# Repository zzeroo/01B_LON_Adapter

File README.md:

## Dateien
- 164.001.01B_ADP_LON_20100224.zip -> Original Dateien "Mack Ware GmbH"

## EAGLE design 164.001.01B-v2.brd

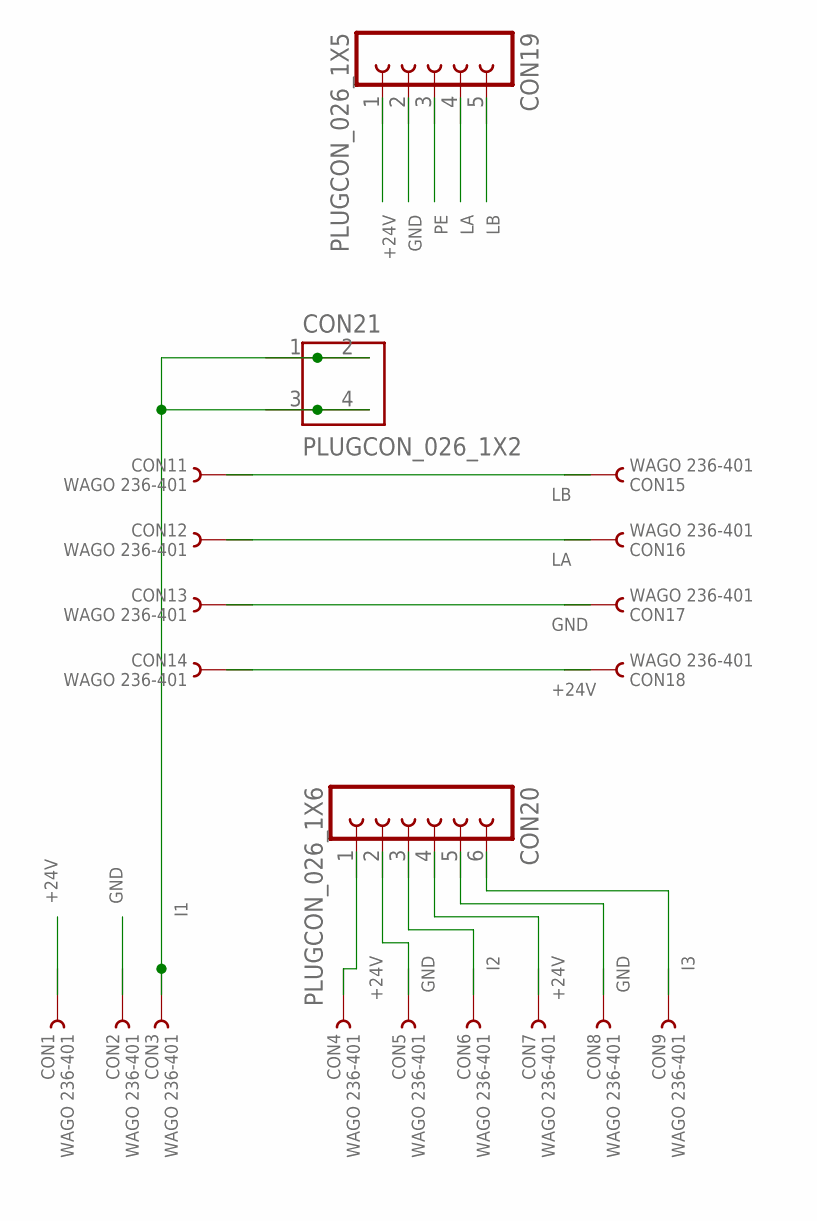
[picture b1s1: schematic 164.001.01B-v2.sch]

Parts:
CON1, CON2, CON3, CON4, CON5, CON6, CON7, CON8, CON9, CON11, CON12, CON13, CON14, CON15, CON16, CON17, CON18: WAGO 236-401; WAGO236
CON19: PLUGCON_026_1X5; PLUGCON1X5
CON20: PLUGCON_026_1X6; PLUGCON1X6
CON21: PLUGCON_026_1X2; PLUGCON1X2

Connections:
+24V: CON1.1, CON1.2, CON4.1, CON4.2, CON7.1, CON7.2, CON14.1, CON14.2, CON18.1, CON18.2, CON19.1, CON19.6, CON20.1, CON20.4, CON20.7, CON20.10
GND: CON2.1, CON2.2, CON5.1, CON5.2, CON8.1, CON8.2, CON13.1, CON13.2, CON17.1, CON17.2, CON19.2, CON19.7, CON20.2, CON20.5, CON20.8, CON20.11
I1: CON3.1, CON3.2, CON21.1, CON21.2 (1), CON21.3 (2), CON21.4 (2)
I2: CON6.1, CON6.2, CON20.3, CON20.9
I3: CON9.1, CON9.2, CON20.6, CON20.12
LA: CON12.1, CON12.2, CON16.1, CON16.2, CON19.4, CON19.9
LB: CON11.1, CON11.2, CON15.1, CON15.2, CON19.5, CON19.10
PE: CON19.3, CON19.8

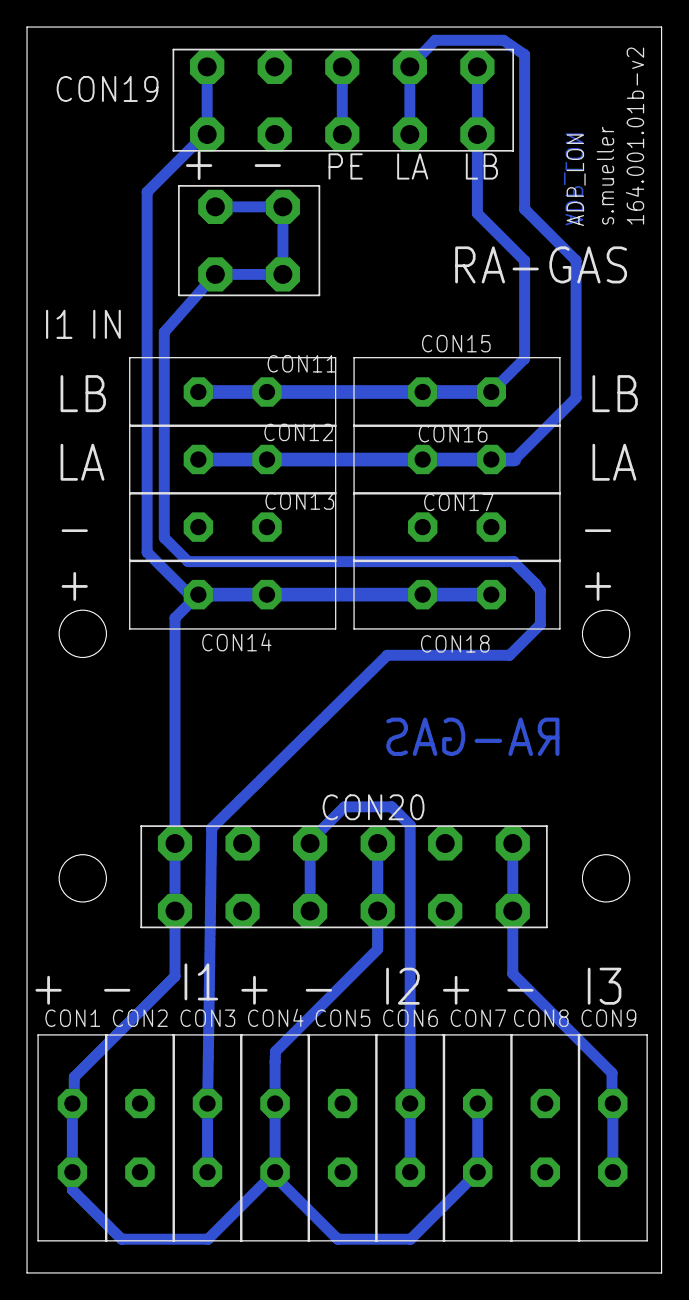
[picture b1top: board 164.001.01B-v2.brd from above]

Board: 2 copper layers, 47.0 x 92.2 mm, 21 parts (0 on the bottom side), 8 nets.

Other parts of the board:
U$1: TITLE

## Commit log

2015-11-18 Initialer Commit mit orgiginal Dateien von "Mack Ware"
2015-11-18 Erste eigene Version, Erste Produktion
    Diese Version wurde am 18.11.2015 über PCB Pool (Conrad
    Leiterplatten Service) produziert.
2015-11-18 Produkt Bezeichnung auf dem Bottom Layer war noch von "Mack Ware"
